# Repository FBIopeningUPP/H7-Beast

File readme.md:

# H7 Beast

H7 Beast is a small open source flight controller that is based of Betaflight, INav, ArduPilot and PX4 firmware. The size of the board with the features is amazing it's just 58x34mm wide and comes with all the features like external spi and canbus and 12 motor output with a single output for ws2812b leds

## Features

- MCU: STM32H743VIT6
- Gyroscope: 2x ICM-42688-P with low noise 3.3v Rail
- Barometer: DPS310
- Blackbox: Sd Card interface
- UARTs: 7x UARTs
- i2C: 2x i2C, 1 internal and 1 external
- SPI: 4x SPI, 3x internal 1x external
- CAN: 1x External Can
- Digital VTX Out: 1x
- MIC5219 low-noise LDO regulators

## Betaflight, INav, ArduPilot and PX4 firmware

As i have used the hardware definition by MatekH743 we can already see the target available in the configurator

# PCB Design

This is my first ever 8 layer design for a compact wing based fliht controller, so it is a bit messy but functional

With a Non-BGA chip i have the design pretty easy and managable with 8 layers, and it can fit small uavs easily, it comes with 5v circuit protection from external esc's and 5v from usb input

This can be powered through external 5v bec from the esc's or any other 5v power source

# Steps to reproduce

U can upload the [gerber](production/h7.zip) to the JLCPCB and select 1oz ENIG and 1oz copper for inner layer
For the assembly we only need the front side to be assembled so we can choose that and then upload the [bom](production/bom.csv) and [designator](production/designators.csv) files to get a quote on the bom and u can order the project

But if u want to hand assmeble the whole thing u can also do that by using [Interactive BOM](h7/bom/ibom.html)
It lists all the components and u can select what all part u have sourced and what all parts are needed to be sourced and what u have placed and what not u have placed on the board

### USAGE OF AI

the ai was used to create [pinout](pinout.md) i copied the hwdef from ardupilot github repo and used ai to create a pinout for me so its easier for me to update things in kicad

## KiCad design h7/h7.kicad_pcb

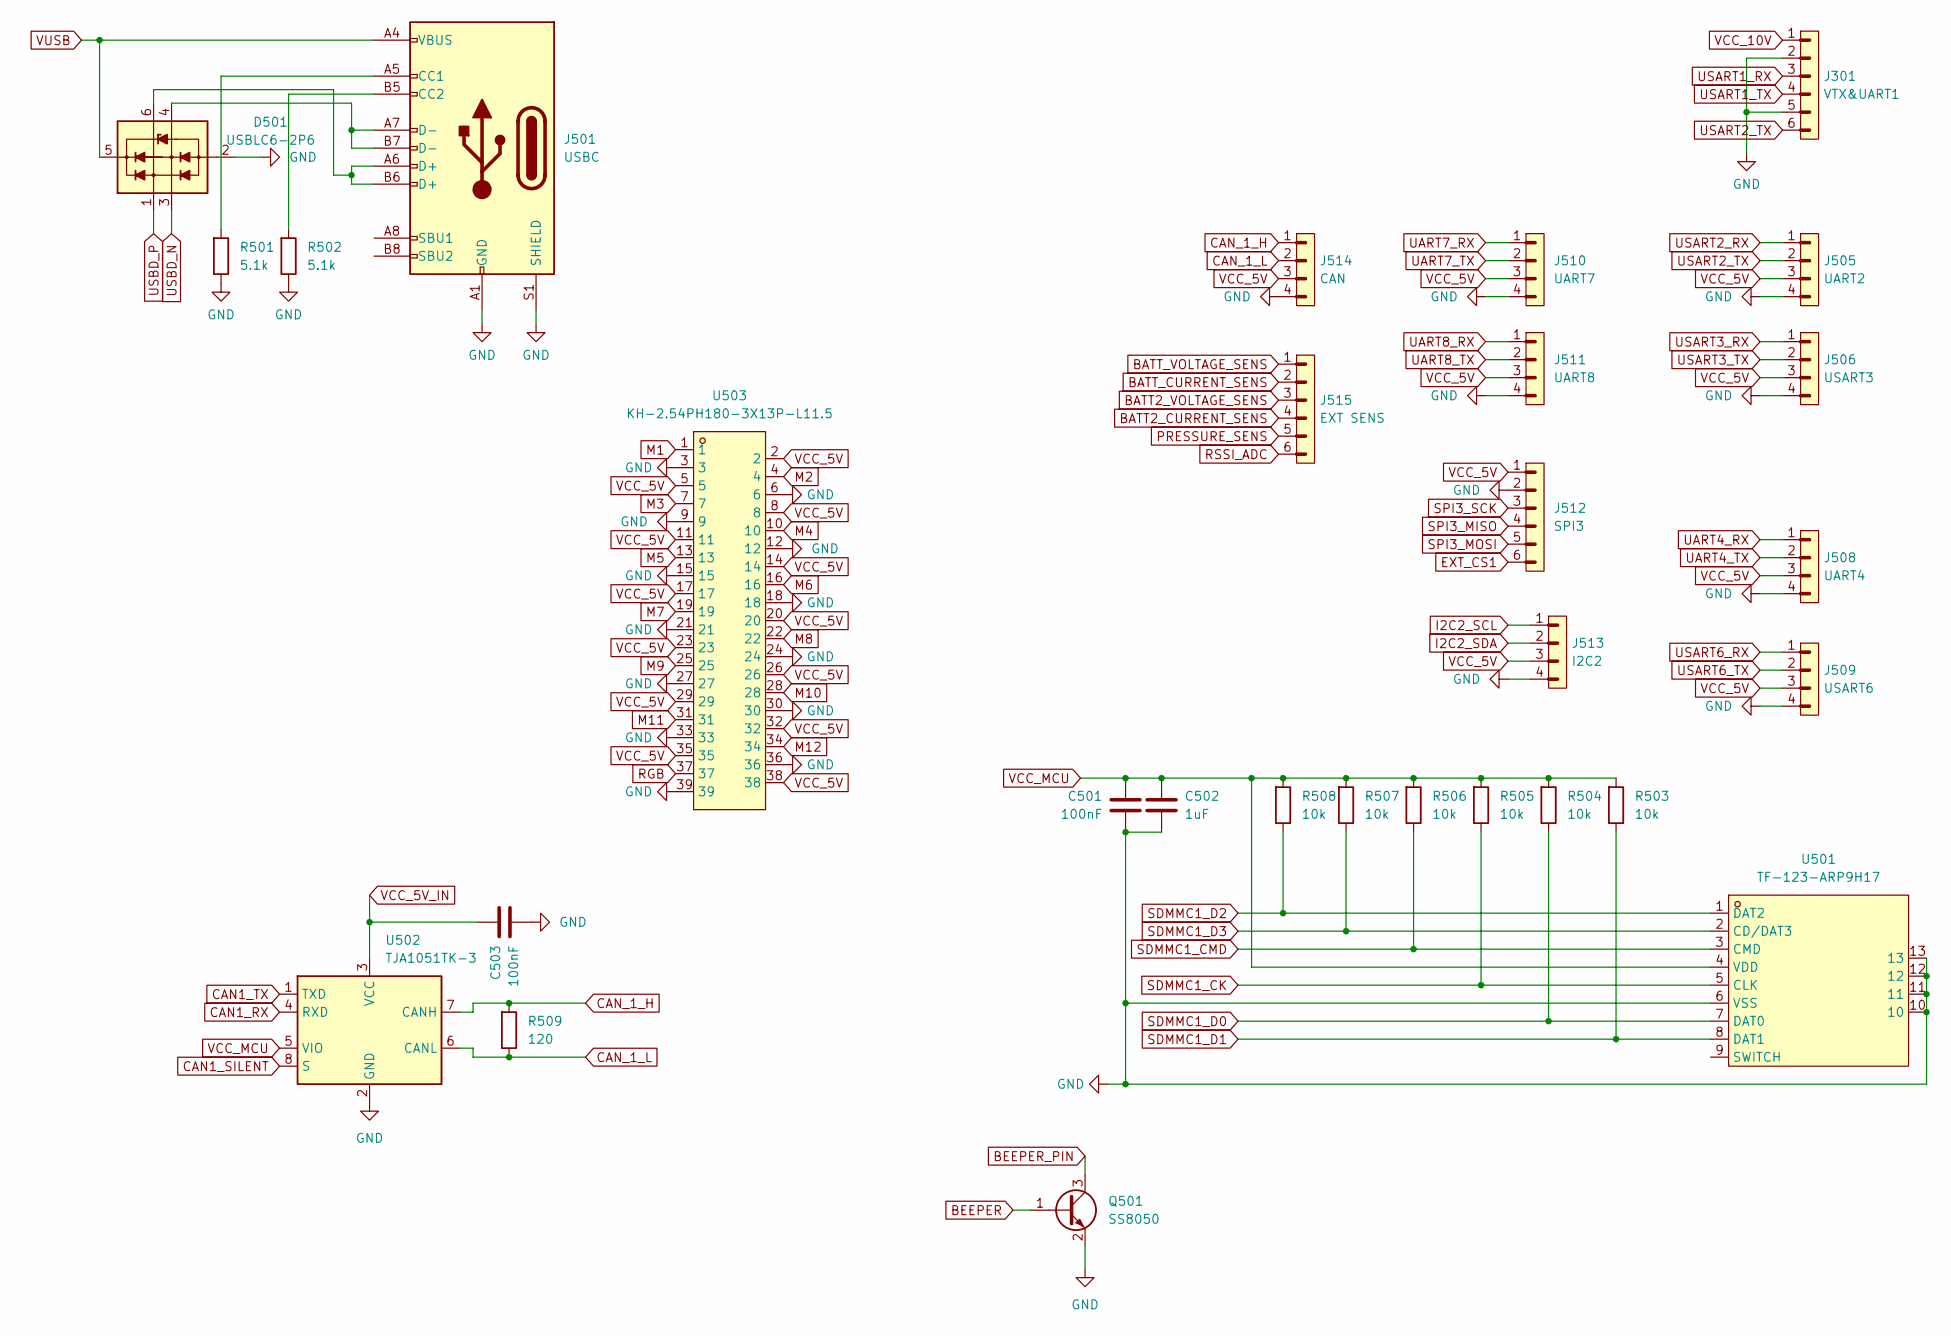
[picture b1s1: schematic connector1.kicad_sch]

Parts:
C501, C503: 100nF; C_0402_1005Metric
C502: 1uF; C_0402_1005Metric
D501: USBLC6-2P6; SOT-666
J301: VTX&UART1; PinHeader_1x06_P2.54mm_Vertical
J501: USBC; USB_C_Receptacle_GCT_USB4105-xx-A_16P_TopMnt_Horizontal
J505: UART2; PinHeader_1x04_P2.54mm_Vertical
J506: USART3; PinHeader_1x04_P2.54mm_Vertical
J508: UART4; PinHeader_1x04_P2.54mm_Vertical
J509: USART6; PinHeader_1x04_P2.54mm_Vertical
J510: UART7; PinHeader_1x04_P2.54mm_Vertical
J511: UART8; PinHeader_1x04_P2.54mm_Vertical
J512: SPI3; PinHeader_1x06_P2.54mm_Vertical
J513: I2C2; PinHeader_1x04_P2.54mm_Vertical
J514: CAN; PinHeader_1x04_P2.54mm_Vertical
J515: EXT SENS; PinHeader_1x06_P2.54mm_Vertical
Q501: SS8050; SOT-23
R501, R502: 5.1k; R_0402_1005Metric
R503, R504, R505, R506, R507, R508: 10k; R_0402_1005Metric
R509: 120; R_0402_1005Metric
U501: TF-123-ARP9H17; TF-SMD_TF-123-ARP9H15; LCSC Part C2982548
U502: TJA1051TK-3; HVSON-8-1EP_3x3mm_P0.65mm_EP1.6x2.4mm
U503: KH-2.54PH180-3X13P-L11.5; HDR-TH_39P-P2.54-V-M-R3-C13-S2.54; MPN KH-2.54PH180-3X13P-L11.5; LCSC Part C20610260

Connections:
BATT2_CURRENT_SENS: J515.4; also elsewhere on the board
BATT2_VOLTAGE_SENS: J515.3; also elsewhere on the board
BATT_CURRENT_SENS: J515.2; also elsewhere on the board
BATT_VOLTAGE_SENS: J515.1; also elsewhere on the board
BEEPER: Q501.1 (B); also elsewhere on the board
BEEPER_PIN: Q501.3 (C)
CAN1_RX: U502.4 (RXD); also elsewhere on the board
CAN1_SILENT: U502.8 (S); also elsewhere on the board
CAN1_TX: U502.1 (TXD); also elsewhere on the board
CAN_1_H: J514.1, R509.1, U502.7 (CANH)
CAN_1_L: J514.2, R509.2, U502.6 (CANL)
EXT_CS1: J512.6; also elsewhere on the board
GND: C501.2, C502.2, C503.2, D501.2 (VN), J301.2, J301.5, J501.A1 (GND), J501.A12 (GND), J501.B1 (GND), J501.B12 (GND), J501.S1 (SHIELD), J505.4, J506.4, J508.4, J509.4, J510.4, J511.4, J512.2, J513.4, J514.4, Q501.2 (E), R501.2, R502.2, U501.6 (VSS), U501.10, U501.11, U501.12, U501.13, U502.2 (GND), U502.9 (GND), U503.3, U503.6, U503.9, U503.12, U503.15, U503.18, U503.21, U503.24, U503.27, U503.30, U503.33, U503.36, U503.39; also elsewhere on the board
I2C2_SCL: J513.1; also elsewhere on the board
I2C2_SDA: J513.2; also elsewhere on the board
M1: U503.1; also elsewhere on the board
M2: U503.4; also elsewhere on the board
M3: U503.7; also elsewhere on the board
M4: U503.10; also elsewhere on the board
M5: U503.13; also elsewhere on the board
M6: U503.16; also elsewhere on the board
M7: U503.19; also elsewhere on the board
M8: U503.22; also elsewhere on the board
M9: U503.25; also elsewhere on the board
M10: U503.28; also elsewhere on the board
M11: U503.31; also elsewhere on the board
M12: U503.34; also elsewhere on the board
unnamed: D501.6 (L1), J501.A6 (D+), J501.B6 (D+)
unnamed: D501.4 (L2), J501.A7 (D-), J501.B7 (D-)
unnamed: J501.A5 (CC1), R501.1
unnamed: J501.B5 (CC2), R502.1
PRESSURE_SENS: J515.5; also elsewhere on the board
RGB: U503.37; also elsewhere on the board
RSSI_ADC: J515.6; also elsewhere on the board
SDMMC1_CK: R505.2, U501.5 (CLK); also elsewhere on the board
SDMMC1_CMD: R506.2, U501.3 (CMD); also elsewhere on the board
SDMMC1_D0: R504.2, U501.7 (DAT0); also elsewhere on the board
SDMMC1_D1: R503.2, U501.8 (DAT1); also elsewhere on the board
SDMMC1_D2: R508.2, U501.1 (DAT2); also elsewhere on the board
SDMMC1_D3: R507.2, U501.2 (CD/DAT3); also elsewhere on the board
SPI3_MISO: J512.4; also elsewhere on the board
SPI3_MOSI: J512.5; also elsewhere on the board
SPI3_SCK: J512.3; also elsewhere on the board
UART4_RX: J508.1; also elsewhere on the board
UART4_TX: J508.2; also elsewhere on the board
UART7_RX: J510.1; also elsewhere on the board
UART7_TX: J510.2; also elsewhere on the board
UART8_RX: J511.1; also elsewhere on the board
UART8_TX: J511.2; also elsewhere on the board
USART1_RX: J301.3; also elsewhere on the board
USART1_TX: J301.4; also elsewhere on the board
USART2_RX: J505.1; also elsewhere on the board
USART2_TX: J301.6, J505.2; also elsewhere on the board
USART3_RX: J506.1; also elsewhere on the board
USART3_TX: J506.2; also elsewhere on the board
USART6_RX: J509.1; also elsewhere on the board
USART6_TX: J509.2; also elsewhere on the board
USBD_N: D501.3 (L2); also elsewhere on the board
USBD_P: D501.1 (L1); also elsewhere on the board
VCC_5V: J505.3, J506.3, J508.3, J509.3, J510.3, J511.3, J512.1, J513.3, J514.3, U503.2, U503.5, U503.8, U503.11, U503.14, U503.17, U503.20, U503.23, U503.26, U503.29, U503.32, U503.35, U503.38; also elsewhere on the board
VCC_5V_IN: C503.1, U502.3 (VCC); also elsewhere on the board
VCC_10V: J301.1
VCC_MCU: C501.1, C502.1, R503.1, R504.1, R505.1, R506.1, R507.1, R508.1, U501.4 (VDD), U502.5 (VIO); also elsewhere on the board
VUSB: D501.5 (VP), J501.A4 (VBUS), J501.A9 (VBUS), J501.B4 (VBUS), J501.B9 (VBUS); also elsewhere on the board

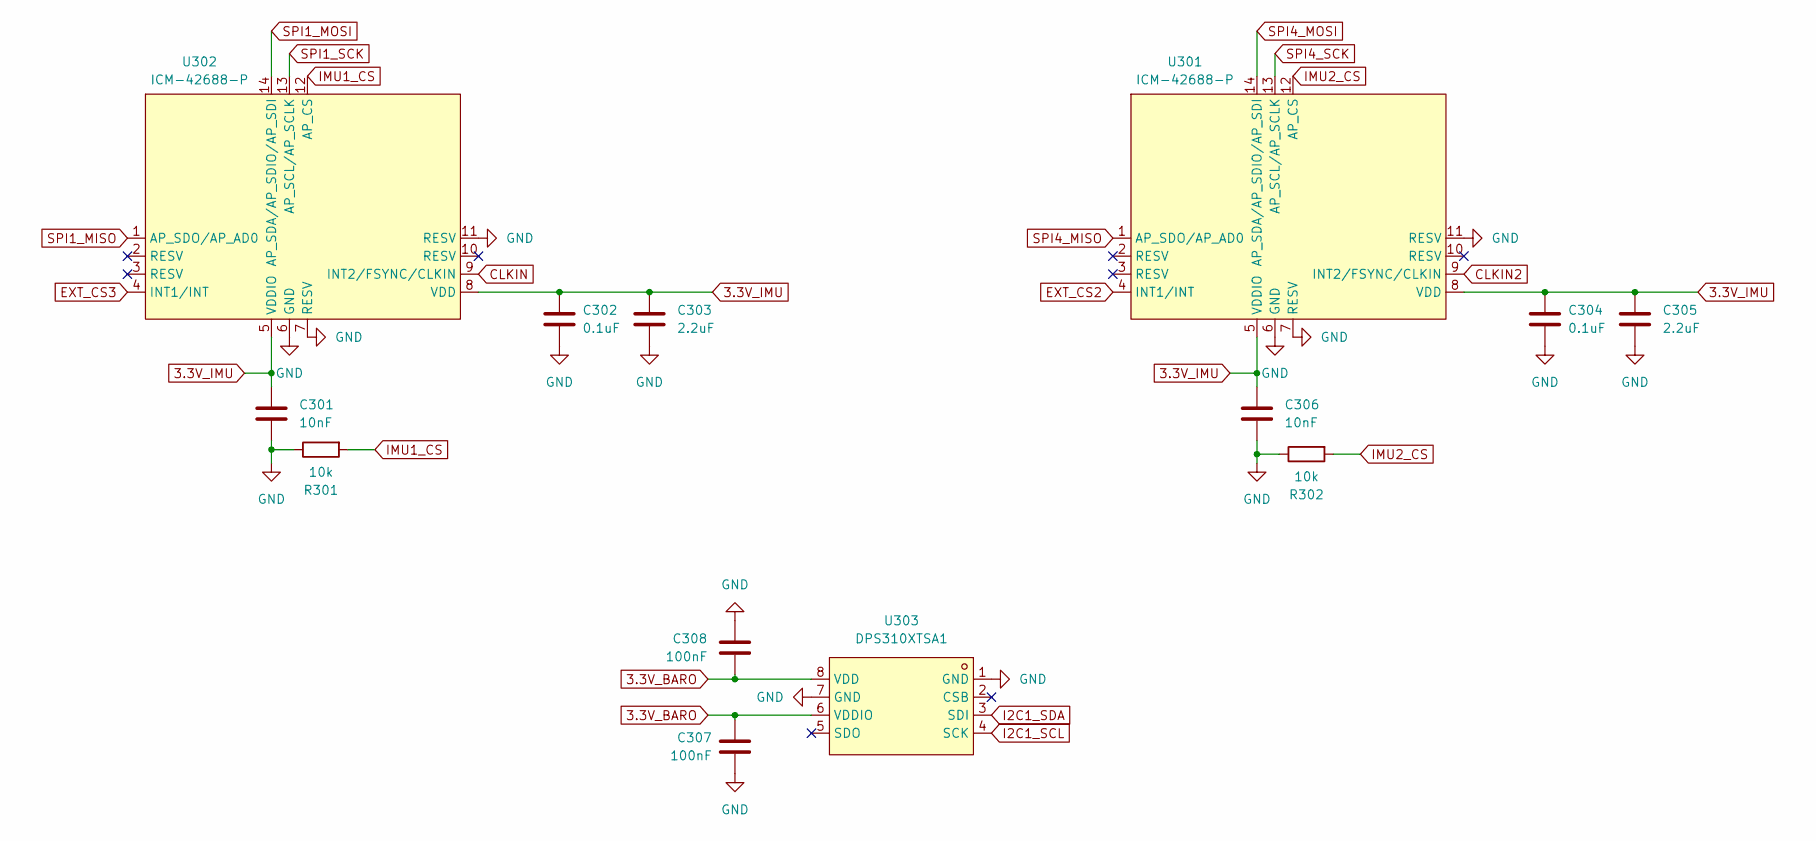
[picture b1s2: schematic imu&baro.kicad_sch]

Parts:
C301, C306: 10nF; C_0402_1005Metric
C302, C304: 0.1uF; C_0402_1005Metric
C303, C305: 2.2uF; C_0402_1005Metric
C307, C308: 100nF; C_0402_1005Metric
R301, R302: 10k; R_0402_1005Metric
U301, U302: ICM-42688-P; LGA-14_L3.0-W2.5-P0.50-TL; LCSC Part C1850418
U303: DPS310XTSA1; LGA-8_DPS310XTSA1; LCSC Part C130156

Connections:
3.3V_BARO: C307.1, C308.1, U303.6 (VDDIO), U303.8 (VDD); also elsewhere on the board
3.3V_IMU: C301.1, C302.1, C303.1, C304.1, C305.1, C306.1, U301.5 (VDDIO), U301.8 (VDD), U302.5 (VDDIO), U302.8 (VDD); also elsewhere on the board
CLKIN: U302.9 (INT2/FSYNC/CLKIN)
CLKIN2: U301.9 (INT2/FSYNC/CLKIN)
EXT_CS2: U301.4 (INT1/INT); also elsewhere on the board
EXT_CS3: U302.4 (INT1/INT); also elsewhere on the board
GND: C301.2, C302.2, C303.2, C304.2, C305.2, C306.2, C307.2, C308.2, R301.2, R302.2, U301.6 (GND), U301.7 (RESV), U301.11 (RESV), U302.6 (GND), U302.7 (RESV), U302.11 (RESV), U303.1 (GND), U303.7 (GND); also elsewhere on the board
I2C1_SCL: U303.4 (SCK); also elsewhere on the board
I2C1_SDA: U303.3 (SDI); also elsewhere on the board
IMU1_CS: R301.1, U302.12 (AP_CS); also elsewhere on the board
IMU2_CS: R302.1, U301.12 (AP_CS); also elsewhere on the board
SPI1_MISO: U302.1 (AP_SDO/AP_AD0); also elsewhere on the board
SPI1_MOSI: U302.14 (AP_SDA/AP_SDIO/AP_SDI); also elsewhere on the board
SPI1_SCK: U302.13 (AP_SCL/AP_SCLK); also elsewhere on the board
SPI4_MISO: U301.1 (AP_SDO/AP_AD0); also elsewhere on the board
SPI4_MOSI: U301.14 (AP_SDA/AP_SDIO/AP_SDI); also elsewhere on the board
SPI4_SCK: U301.13 (AP_SCL/AP_SCLK); also elsewhere on the board

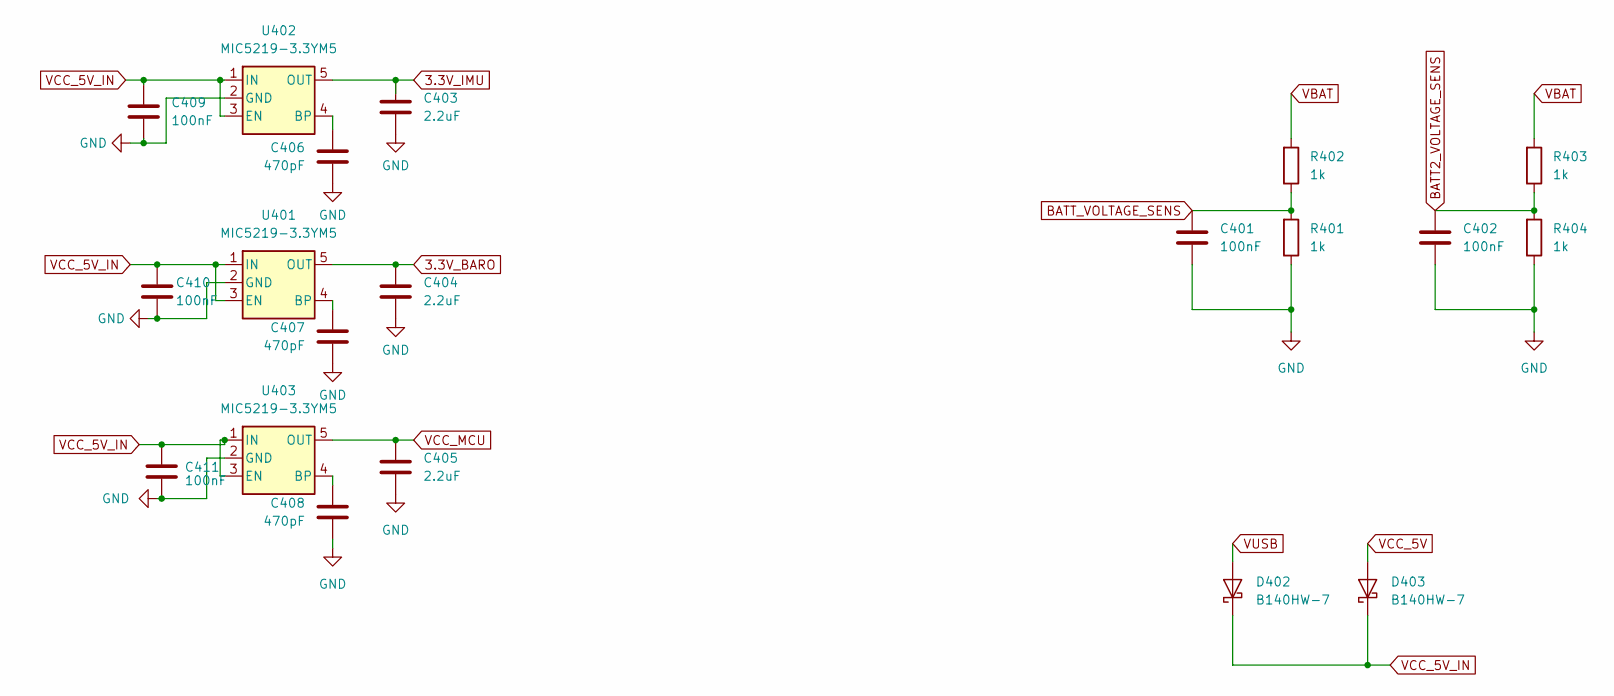
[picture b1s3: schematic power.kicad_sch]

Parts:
C401, C402: 100nF; C_0402_1005Metric
C403, C404, C405: 2.2uF; C_0603_1608Metric
C406, C407, C408: 470pF; C_0603_1608Metric
C409, C410, C411: 100nF; C_0603_1608Metric
D402, D403: B140HW-7; D_SOD-123; Part Number B140HW-7; JLCPCB ID C134429
R401, R402, R403, R404: 1k; R_0402_1005Metric
U401, U402, U403: MIC5219-3.3YM5; SOT-23-5

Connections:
3.3V_BARO: C404.1, U401.5 (OUT); also elsewhere on the board
3.3V_IMU: C403.1, U402.5 (OUT); also elsewhere on the board
BATT2_VOLTAGE_SENS: C402.2, R403.2, R404.1; also elsewhere on the board
BATT_VOLTAGE_SENS: C401.2, R401.1, R402.2; also elsewhere on the board
GND: C401.1, C402.1, C403.2, C404.2, C405.2, C406.2, C407.2, C408.2, C409.1, C410.1, C411.1, R401.2, R404.2, U401.2 (GND), U402.2 (GND), U403.2 (GND); also elsewhere on the board
unnamed: C407.1, U401.4 (BP)
unnamed: C406.1, U402.4 (BP)
unnamed: C408.1, U403.4 (BP)
VBAT: R402.1, R403.1
VCC_5V: D403.2 (A); also elsewhere on the board
VCC_5V_IN: C409.2, C410.2, C411.2, D402.1 (K), D403.1 (K), U401.1 (IN), U401.3 (EN), U402.1 (IN), U402.3 (EN), U403.1 (IN), U403.3 (EN); also elsewhere on the board
VCC_MCU: C405.1, U403.5 (OUT); also elsewhere on the board
VUSB: D402.2 (A); also elsewhere on the board

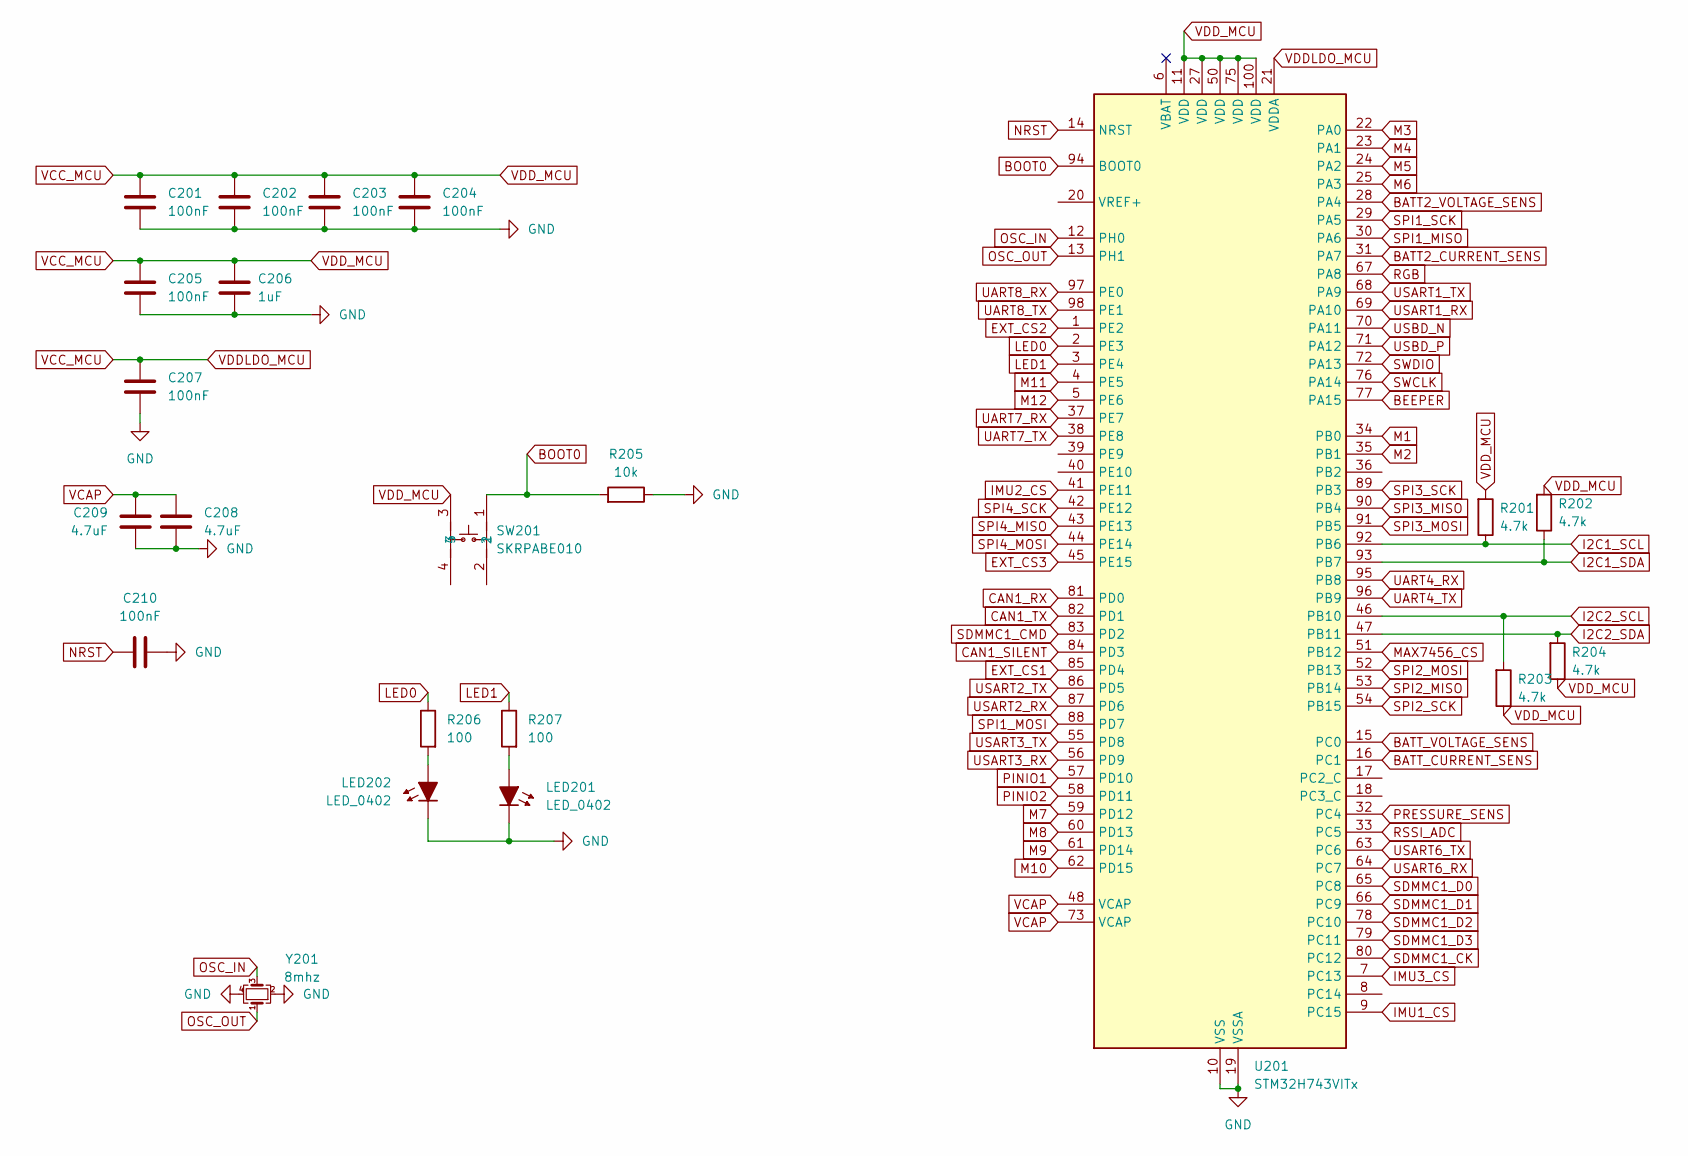
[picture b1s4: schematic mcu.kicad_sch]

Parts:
C201, C202, C203, C204, C205, C207, C210: 100nF; C_0402_1005Metric
C206: 1uF; C_0402_1005Metric
C208, C209: 4.7uF; C_0402_1005Metric
LED201, LED202: LED_0402; LED_0402_1005Metric
R201, R202, R203, R204: 4.7k; R_0402_1005Metric
R205: 10k; R_0402_1005Metric
R206, R207: 100; R_0402_1005Metric
SW201: SKRPABE010; KEY-SMD_4P-L4.2-W3.2-P2.20-LS4.6; LCSC Part C115360
U201: STM32H743VITx; LQFP-100_14x14mm_P0.5mm
Y201: 8mhz; Crystal_SMD_2520-4Pin_2.5x2.0mm

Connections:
BATT2_CURRENT_SENS: U201.31 (PA7); also elsewhere on the board
BATT2_VOLTAGE_SENS: U201.28 (PA4); also elsewhere on the board
BATT_CURRENT_SENS: U201.16 (PC1); also elsewhere on the board
BATT_VOLTAGE_SENS: U201.15 (PC0); also elsewhere on the board
BEEPER: U201.77 (PA15); also elsewhere on the board
BOOT0: R205.1, SW201.1, U201.94 (BOOT0)
CAN1_RX: U201.81 (PD0); also elsewhere on the board
CAN1_SILENT: U201.84 (PD3); also elsewhere on the board
CAN1_TX: U201.82 (PD1); also elsewhere on the board
EXT_CS1: U201.85 (PD4); also elsewhere on the board
EXT_CS2: U201.1 (PE2); also elsewhere on the board
EXT_CS3: U201.45 (PE15); also elsewhere on the board
GND: C201.2, C202.2, C203.2, C204.2, C205.2, C206.2, C207.2, C208.2, C209.2, C210.2, LED201.1 (K), LED202.1 (K), R205.2, U201.10 (VSS), U201.19 (VSSA), U201.26 (VSS), U201.49 (VSS), U201.74 (VSS), U201.99 (VSS), Y201.2, Y201.4; also elsewhere on the board
I2C1_SCL: R201.2, U201.92 (PB6); also elsewhere on the board
I2C1_SDA: R202.2, U201.93 (PB7); also elsewhere on the board
I2C2_SCL: R203.1, U201.46 (PB10); also elsewhere on the board
I2C2_SDA: R204.1, U201.47 (PB11); also elsewhere on the board
IMU1_CS: U201.9 (PC15); also elsewhere on the board
IMU2_CS: U201.41 (PE11); also elsewhere on the board
IMU3_CS: U201.7 (PC13)
LED0: R206.2, U201.2 (PE3)
LED1: R207.2, U201.3 (PE4)
M1: U201.34 (PB0); also elsewhere on the board
M2: U201.35 (PB1); also elsewhere on the board
M3: U201.22 (PA0); also elsewhere on the board
M4: U201.23 (PA1); also elsewhere on the board
M5: U201.24 (PA2); also elsewhere on the board
M6: U201.25 (PA3); also elsewhere on the board
M7: U201.59 (PD12); also elsewhere on the board
M8: U201.60 (PD13); also elsewhere on the board
M9: U201.61 (PD14); also elsewhere on the board
M10: U201.62 (PD15); also elsewhere on the board
M11: U201.4 (PE5); also elsewhere on the board
M12: U201.5 (PE6); also elsewhere on the board
MAX7456_CS: U201.51 (PB12)
NRST: C210.1, U201.14 (NRST)
unnamed: LED201.2 (A), R207.1
unnamed: LED202.2 (A), R206.1
OSC_IN: U201.12 (PH0), Y201.3
OSC_OUT: U201.13 (PH1), Y201.1
PINIO1: U201.57 (PD10)
PINIO2: U201.58 (PD11)
PRESSURE_SENS: U201.32 (PC4); also elsewhere on the board
RGB: U201.67 (PA8); also elsewhere on the board
RSSI_ADC: U201.33 (PC5); also elsewhere on the board
SDMMC1_CK: U201.80 (PC12); also elsewhere on the board
SDMMC1_CMD: U201.83 (PD2); also elsewhere on the board
SDMMC1_D0: U201.65 (PC8); also elsewhere on the board
SDMMC1_D1: U201.66 (PC9); also elsewhere on the board
SDMMC1_D2: U201.78 (PC10); also elsewhere on the board
SDMMC1_D3: U201.79 (PC11); also elsewhere on the board
SPI1_MISO: U201.30 (PA6); also elsewhere on the board
SPI1_MOSI: U201.88 (PD7); also elsewhere on the board
SPI1_SCK: U201.29 (PA5); also elsewhere on the board
SPI2_MISO: U201.53 (PB14)
SPI2_MOSI: U201.52 (PB13)
SPI2_SCK: U201.54 (PB15)
SPI3_MISO: U201.90 (PB4); also elsewhere on the board
SPI3_MOSI: U201.91 (PB5); also elsewhere on the board
SPI3_SCK: U201.89 (PB3); also elsewhere on the board
SPI4_MISO: U201.43 (PE13); also elsewhere on the board
SPI4_MOSI: U201.44 (PE14); also elsewhere on the board
SPI4_SCK: U201.42 (PE12); also elsewhere on the board
SWCLK: U201.76 (PA14)
SWDIO: U201.72 (PA13)
UART4_RX: U201.95 (PB8); also elsewhere on the board
UART4_TX: U201.96 (PB9); also elsewhere on the board
UART7_RX: U201.37 (PE7); also elsewhere on the board
UART7_TX: U201.38 (PE8); also elsewhere on the board
UART8_RX: U201.97 (PE0); also elsewhere on the board
UART8_TX: U201.98 (PE1); also elsewhere on the board
USART1_RX: U201.69 (PA10); also elsewhere on the board
USART1_TX: U201.68 (PA9); also elsewhere on the board
USART2_RX: U201.87 (PD6); also elsewhere on the board
USART2_TX: U201.86 (PD5); also elsewhere on the board
USART3_RX: U201.56 (PD9); also elsewhere on the board
USART3_TX: U201.55 (PD8); also elsewhere on the board
USART6_RX: U201.64 (PC7); also elsewhere on the board
USART6_TX: U201.63 (PC6); also elsewhere on the board
USBD_N: U201.70 (PA11); also elsewhere on the board
USBD_P: U201.71 (PA12); also elsewhere on the board
VCAP: C208.1, C209.1, U201.48 (VCAP), U201.73 (VCAP)
VCC_MCU: C201.1, C202.1, C203.1, C204.1, C205.1, C206.1, C207.1, R201.1, R202.1, R203.2, R204.2, SW201.3, U201.11 (VDD), U201.21 (VDDA), U201.27 (VDD), U201.50 (VDD), U201.75 (VDD), U201.100 (VDD); also elsewhere on the board

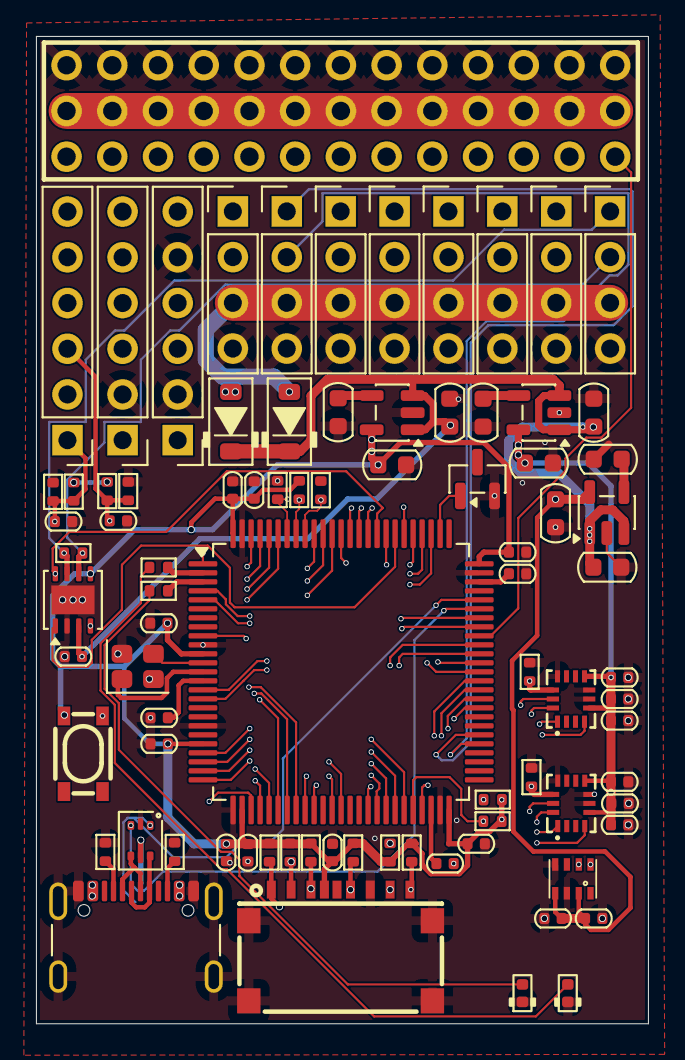
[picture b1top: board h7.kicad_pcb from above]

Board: 8 copper layers, 34.0 x 54.8 mm, 84 parts (0 on the bottom side), 89 nets.

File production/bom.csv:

Designator,Footprint,Quantity,Value,LCSC Part #
"C201, C202, C203, C204, C205, C207, C210, C307, C308, C401, C402, C501, C503",0402,13,100nF,
"C206, C502",0402,2,1uF,
"C208, C209",0402,2,4.7uF,
"C301, C306",0402,2,10nF,
"C302, C304",0402,2,0.1uF,
"C303, C305",0402,2,2.2uF,
"C403, C404, C405",0603,3,2.2uF,
"C406, C407, C408",0603,3,470pF,
"C409, C410, C411",0603,3,100nF,
"D402, D403",D_SOD-123,2,B140HW-7,
D501,SOT-666,1,USBLC6-2P6,
J301,PinHeader_1x06_P2.54mm_Vertical,1,VTX&UART1,
J501,USB_C_Receptacle_GCT_USB4105-xx-A_16P_TopMnt_Horizontal,1,USBC,
J505,PinHeader_1x04_P2.54mm_Vertical,1,UART2,
J506,PinHeader_1x04_P2.54mm_Vertical,1,USART3,
J508,PinHeader_1x04_P2.54mm_Vertical,1,UART4,
J509,PinHeader_1x04_P2.54mm_Vertical,1,USART6,
J510,PinHeader_1x04_P2.54mm_Vertical,1,UART7,
J511,PinHeader_1x04_P2.54mm_Vertical,1,UART8,
J512,PinHeader_1x06_P2.54mm_Vertical,1,SPI3,
J513,PinHeader_1x04_P2.54mm_Vertical,1,I2C2,
J514,PinHeader_1x04_P2.54mm_Vertical,1,CAN,
J515,PinHeader_1x06_P2.54mm_Vertical,1,EXT SENS,
"LED201, LED202",0402,2,LED_0402,
Q501,SOT-23,1,SS8050,
"R201, R202, R203, R204",0402,4,4.7k,
"R205, R301, R302, R503, R504, R505, R506, R507, R508",0402,9,10k,
"R206, R207",0402,2,100,
"R401, R402, R403, R404",0402,4,1k,
"R501, R502",0402,2,5.1k,
R509,0402,1,120,
SW201,KEY-SMD_4P-L4.2-W3.2-P2.20-LS4.6,1,SKRPABE010,C115360
U201,LQFP-100_14x14mm_P0.5mm,1,STM32H743VITx,
"U301, U302",LGA-14_L3.0-W2.5-P0.50-TL,2,ICM-42688-P,C1850418
U303,LGA-8_DPS310XTSA1,1,DPS310XTSA1,C130156
"U401, U402, U403",SOT-23-5,3,MIC5219-3.3YM5,
U501,TF-SMD_TF-123-ARP9H15,1,TF-123-ARP9H17,C2982548
U502,HVSON-8-1EP_3x3mm_P0.65mm_EP1.6x2.4mm,1,TJA1051TK-3,
U503,HDR-TH_39P-P2.54-V-M-R3-C13-S2.54,1,KH-2.54PH180-3X13P-L11.5,C20610260
Y201,Crystal_SMD_2520-4Pin_2.5x2.0mm,1,8mhz,
